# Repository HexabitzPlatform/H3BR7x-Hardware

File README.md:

# H3BR7x-Hardware
Hexabitz 6-Digit 7-Segment Red Display Module Hardware Design

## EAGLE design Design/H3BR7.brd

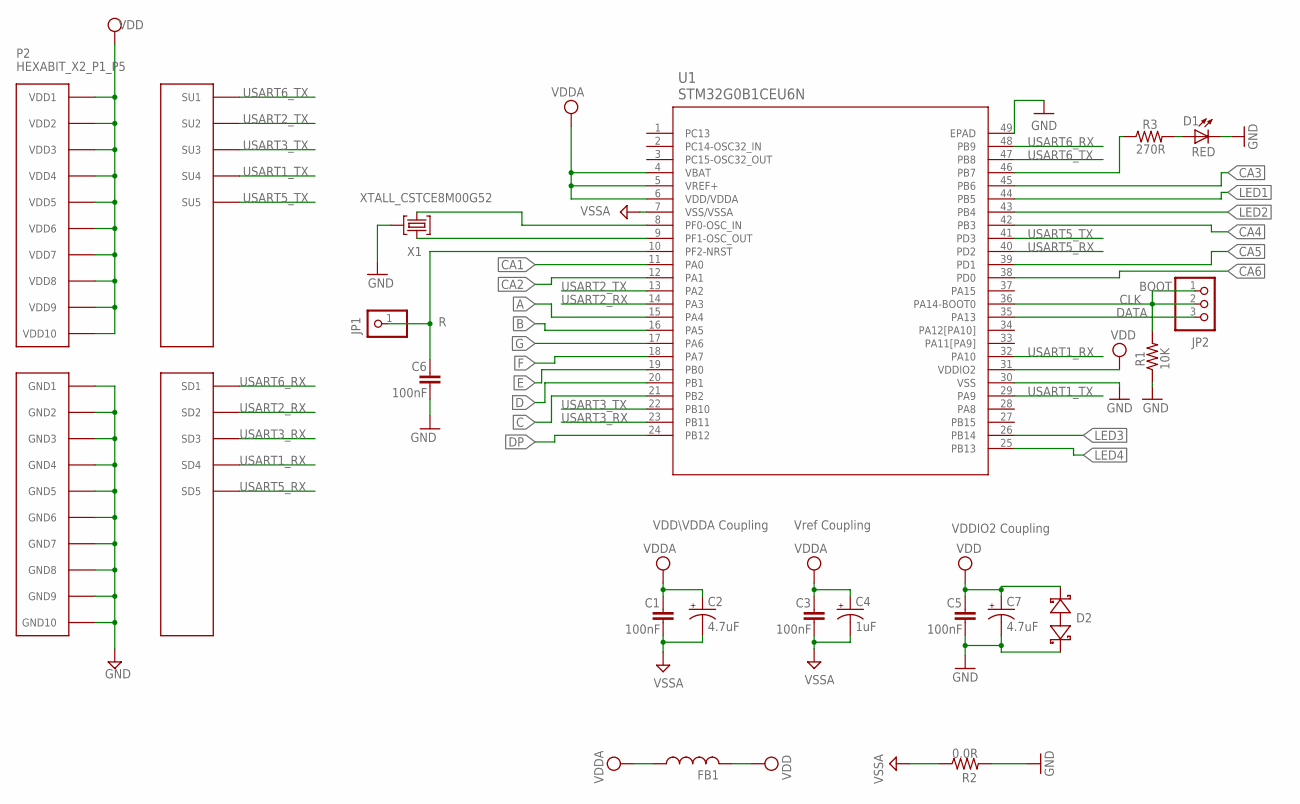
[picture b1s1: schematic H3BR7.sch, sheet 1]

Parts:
C1, C3, C5, C6: 100nF; C-0603
C2, C7: 4.7uF; C-0805-POL
C4: 1uF; C-0805-POL
D1: RED; VLMS1300-GS08; MPN VLMS1300-GS08
D2: BOURNS_CDSOD323-T03SCBOURNS_CDSOD323-T03SC_0_0; BOURNS_CDSOD323-T03SC_0
FB1: FB-0603
JP1: R; 1X01
JP2: PINHD-1X3; 1X03
P2: HEXABIT_X2_P1_P5; HEXABIT_17.32_X2_P1_P5
R1: 10K; R-0603
R2: 0.0R; R-0603
R3: 270R; R-0603
U1: STM32G0B1CEU6N; HEXABITZ_ICS_QFN_B1CEU6_STM-L
X1: XTALL_CSTCE8M00G52

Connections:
A: U1.15 (PA4); also elsewhere on the board
B: U1.16 (PA5); also elsewhere on the board
C: U1.21 (PB2); also elsewhere on the board
CA1: U1.11 (PA0); also elsewhere on the board
CA2: U1.12 (PA1); also elsewhere on the board
CA3: U1.45 (PB6); also elsewhere on the board
CA4: U1.42 (PB3); also elsewhere on the board
CA5: U1.39 (PD1); also elsewhere on the board
CA6: U1.38 (PD0); also elsewhere on the board
CLK: JP2.1, JP2.2, R1.2, U1.36 (PA14-BOOT0)
D: U1.20 (PB1); also elsewhere on the board
DATA: JP2.3, U1.35 (PA13)
DP: U1.24 (PB12); also elsewhere on the board
E: U1.19 (PB0); also elsewhere on the board
F: U1.18 (PA7); also elsewhere on the board
G: U1.17 (PA6); also elsewhere on the board
GND: C5.2, C6.2, C7.2 (-), D1.C, D2.1 (A), P2.PAD_PD11 (GND1), P2.PAD_PD12 (GND2), P2.PAD_PD13 (GND3), P2.PAD_PD14 (GND4), P2.PAD_PD15 (GND5), P2.PAD_PD16 (GND6), P2.PAD_PD17 (GND7), P2.PAD_PD18 (GND8), P2.PAD_PD19 (GND9), P2.PAD_PD20 (GND10), R1.1, R2.2, U1.30 (VSS), U1.49 (EPAD), X1.P$2 (2); also elsewhere on the board
LED1: U1.44 (PB5); also elsewhere on the board
LED2: U1.43 (PB4); also elsewhere on the board
LED3: U1.26 (PB14); also elsewhere on the board
LED4: U1.25 (PB13); also elsewhere on the board
unnamed: D1.A, R3.2
unnamed: R3.1, U1.46 (PB7)
unnamed: U1.9 (PF1-OSC_OUT), X1.P$1 (1)
unnamed: U1.8 (PF0-OSC_IN), X1.P$3 (3)
unnamed: C6.1, JP1.1, U1.10 (PF2-NRST)
USART1_RX: P2.PAD_PD4 (SD4), U1.32 (PA10)
USART1_TX: P2.PAD_PU4 (SU4), U1.29 (PA9)
USART2_RX: P2.PAD_PD2 (SD2), U1.14 (PA3)
USART2_TX: P2.PAD_PU2 (SU2), U1.13 (PA2)
USART3_RX: P2.PAD_PD3 (SD3), U1.23 (PB11)
USART3_TX: P2.PAD_PU3 (SU3), U1.22 (PB10)
USART5_RX: P2.PAD_PD5 (SD5), U1.40 (PD2)
USART5_TX: P2.PAD_PU5 (SU5), U1.41 (PD3)
USART6_RX: P2.PAD_PD1 (SD1), U1.48 (PB9)
USART6_TX: P2.PAD_PU1 (SU1), U1.47 (PB8)
VDD: C5.1, C7.1 (+), D2.2 (C), FB1.2, P2.PAD_PU11 (VDD1), P2.PAD_PU12 (VDD2), P2.PAD_PU13 (VDD3), P2.PAD_PU14 (VDD4), P2.PAD_PU15 (VDD5), P2.PAD_PU16 (VDD6), P2.PAD_PU17 (VDD7), P2.PAD_PU18 (VDD8), P2.PAD_PU19 (VDD9), P2.PAD_PU20 (VDD10), U1.31 (VDDIO2); also elsewhere on the board
VDDA: C1.1, C2.1 (+), C3.1, C4.1 (+), FB1.1, U1.4 (VBAT), U1.5 (VREF+), U1.6 (VDD/VDDA)
VSSA: C1.2, C2.2 (-), C3.2, C4.2 (-), R2.1, U1.7 (VSS/VSSA)

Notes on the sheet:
Vref Coupling
VDDIO2 Coupling
VDD\VDDA Coupling
BOOT

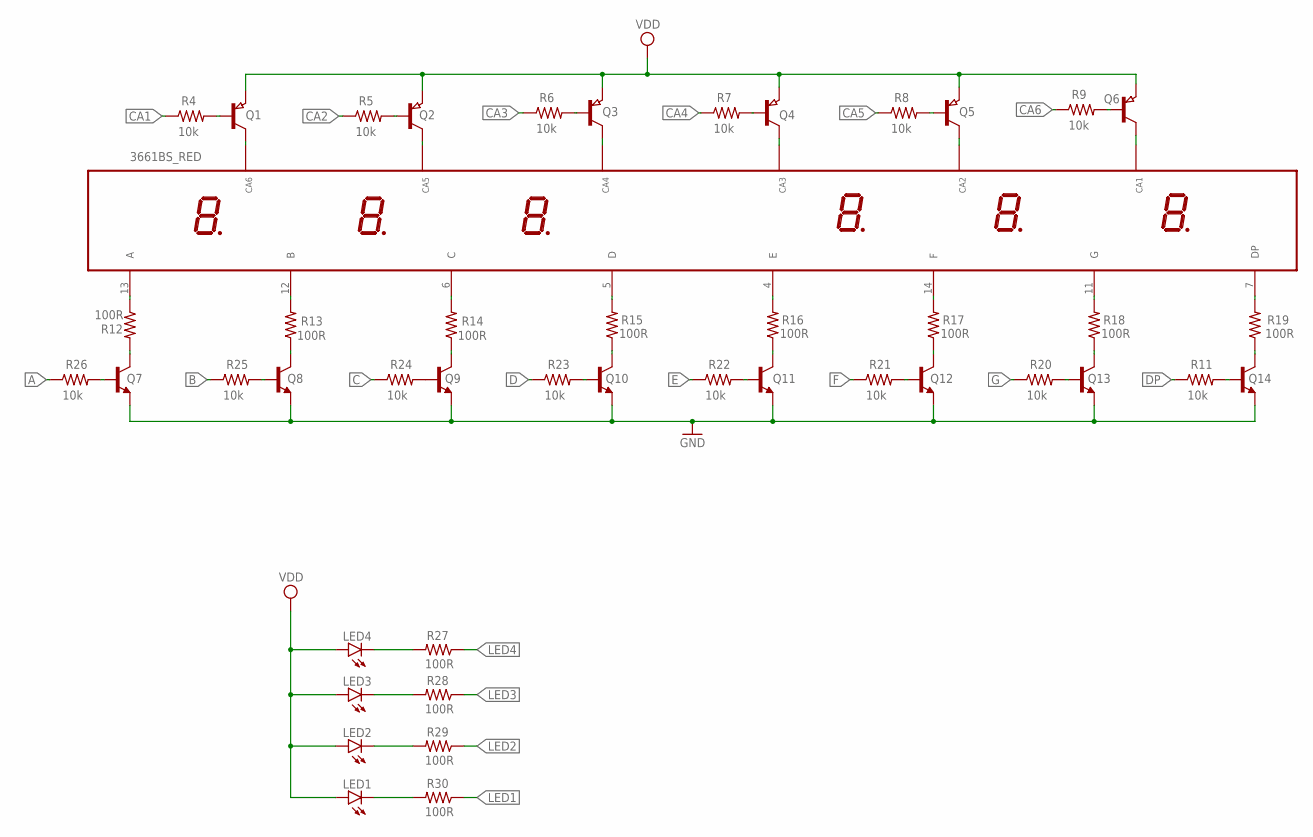
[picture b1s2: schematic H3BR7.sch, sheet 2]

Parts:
3661BS: 3661BS_RED; 3661BS
LED1, LED2, LED3, LED4: LED-3MM3MM; LED3MM
Q1, Q2, Q3, Q4, Q5, Q6: SEMICON-SMD-IPC_PNP-TRANSISTOR_SOT23; SEMICON-SMD-IPC_SOT23
Q7, Q8, Q9, Q10, Q11, Q12, Q13, Q14: MMBT3904LT1
R4, R5, R6, R7, R8, R9, R11, R20, R21, R22, R23, R24, R25, R26: 10k; R-0603
R12, R13, R14, R15, R16, R17, R18, R19, R27, R28, R29, R30: 100R; R-0603
TRIMBLE-LOGO1: HEXA-LOGO

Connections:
A: R26.1; also elsewhere on the board
B: R25.1; also elsewhere on the board
C: R24.1; also elsewhere on the board
CA1: R4.1; also elsewhere on the board
CA2: R5.1; also elsewhere on the board
CA3: R6.1; also elsewhere on the board
CA4: R7.1; also elsewhere on the board
CA5: R8.1; also elsewhere on the board
CA6: R9.1; also elsewhere on the board
D: R23.1; also elsewhere on the board
DP: R11.1; also elsewhere on the board
E: R22.1; also elsewhere on the board
F: R21.1; also elsewhere on the board
G: R20.1; also elsewhere on the board
GND: Q7.2 (E), Q8.2 (E), Q9.2 (E), Q10.2 (E), Q11.2 (E), Q12.2 (E), Q13.2 (E), Q14.2 (E); also elsewhere on the board
LED1: R30.1; also elsewhere on the board
LED2: R29.1; also elsewhere on the board
LED3: R28.1; also elsewhere on the board
LED4: R27.1; also elsewhere on the board
unnamed: 3661BS.13 (A), R12.1
unnamed: Q7.1 (B), R26.2
unnamed: Q8.3 (C), R13.1
unnamed: 3661BS.6 (C), R14.2
unnamed: Q8.1 (B), R25.2
unnamed: Q9.1 (B), R24.2
unnamed: Q10.1 (B), R23.2
unnamed: Q11.1 (B), R22.2
unnamed: Q12.1 (B), R21.2
unnamed: Q13.1 (B), R20.2
unnamed: Q14.1 (B), R11.2
unnamed: Q10.3 (C), R15.1
unnamed: 3661BS.5 (D), R15.2
unnamed: Q11.3 (C), R16.1
unnamed: Q13.3 (C), R18.1
unnamed: 3661BS.11 (G), R18.2
unnamed: Q7.3 (C), R12.2
unnamed: LED4.K (C), R27.2
unnamed: LED3.K (C), R28.2
unnamed: Q1.1 (B), R4.2
unnamed: Q2.1 (B), R5.2
unnamed: Q3.1 (B), R6.2
unnamed: Q4.1 (B), R7.2
unnamed: Q5.1 (B), R8.2
unnamed: Q6.1 (B), R9.2
unnamed: 3661BS.1 (CA), Q6.3 (C)
unnamed: LED2.K (C), R29.2
unnamed: LED1.K (C), R30.2
unnamed: 3661BS.8 (CA), Q1.3 (C)
unnamed: 3661BS.9 (CA), Q2.3 (C)
unnamed: 3661BS.10 (CA), Q3.3 (C)
unnamed: 3661BS.3 (CA), Q4.3 (C)
unnamed: 3661BS.2 (CA), Q5.3 (C)
unnamed: 3661BS.7 (DP), R19.2
unnamed: Q14.3 (C), R19.1
unnamed: 3661BS.4 (E), R16.2
unnamed: 3661BS.14 (F), R17.2
unnamed: 3661BS.12 (B), R13.2
unnamed: Q12.3 (C), R17.1
unnamed: Q9.3 (C), R14.1
VDD: LED1.A, LED2.A, LED3.A, LED4.A, Q1.2 (E), Q2.2 (E), Q3.2 (E), Q4.2 (E), Q5.2 (E), Q6.2 (E); also elsewhere on the board

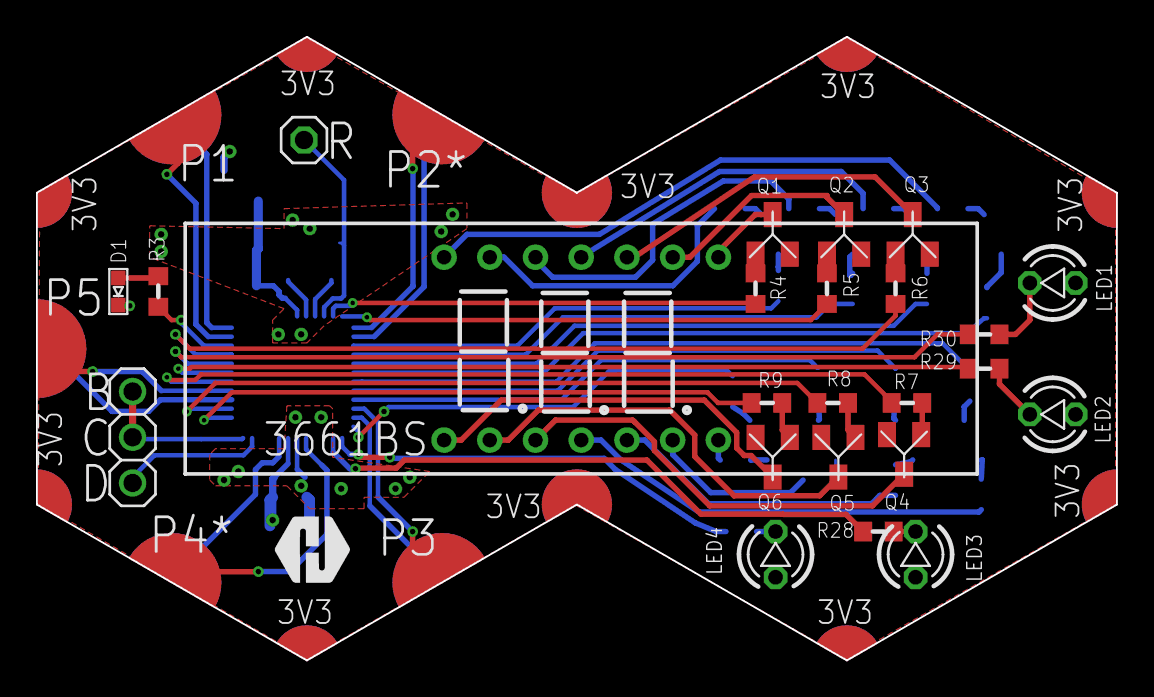
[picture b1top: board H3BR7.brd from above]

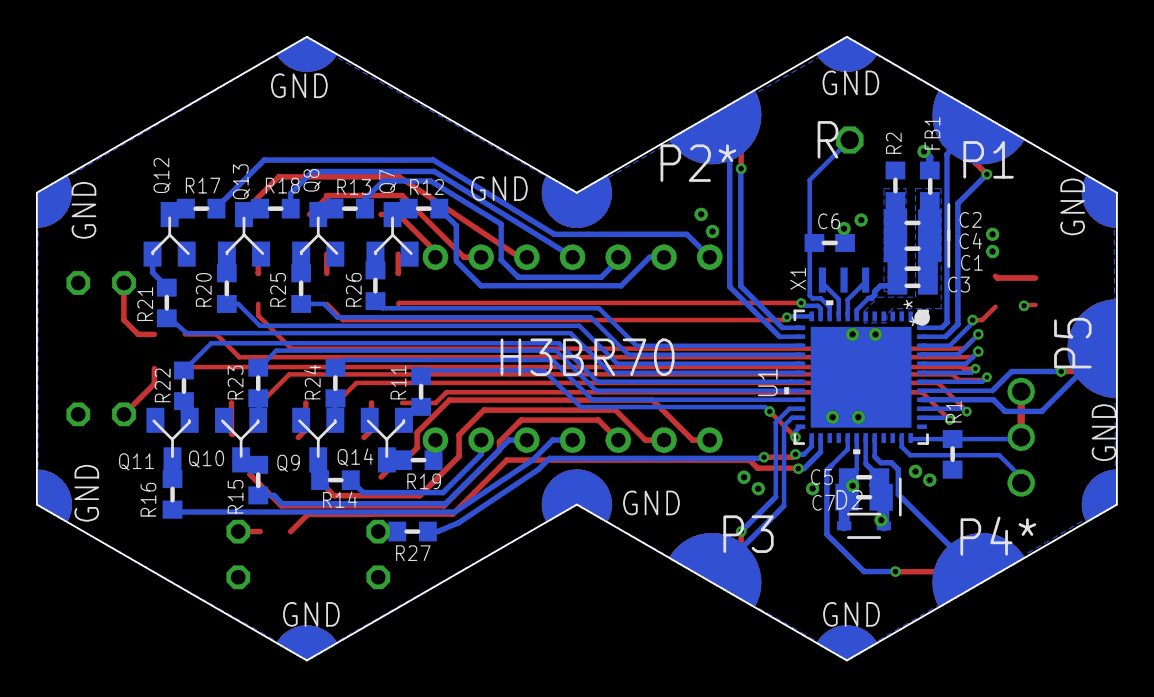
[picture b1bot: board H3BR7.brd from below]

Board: 2 copper layers, 60.0 x 34.6 mm, 64 parts (38 on the bottom side), 79 nets.

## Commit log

2024-02-12 Reviewed Version, all finished.
2024-04-25 -Add Tvs diode -Update the LOGO -Fix the clearance and soldermask layer issues

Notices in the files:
parts and their libraries:
HEXABITZ_ICs: COPYRIGHT: Copyright (C) 2022 Ultra Librarian. All rights reserved.
